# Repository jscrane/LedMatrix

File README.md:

View this project on [CADLAB.io](https://cadlab.io/project/1792). 

# LedMatrix
Simple LED Matrix driver library for LEDs which are driven directly from
GPIOs. Supports square LEDs up to 8x8.

## Requirements
- Arduino 1.8.x
- [SimpleTimer](https://github.com/jfturcot/SimpleTimer) library (for examples)

## Other
See [blog article](https://programmablehardware.blogspot.com/2019/05/soldering-kata.html).

Prototype 7x7 assembled on stripboard:

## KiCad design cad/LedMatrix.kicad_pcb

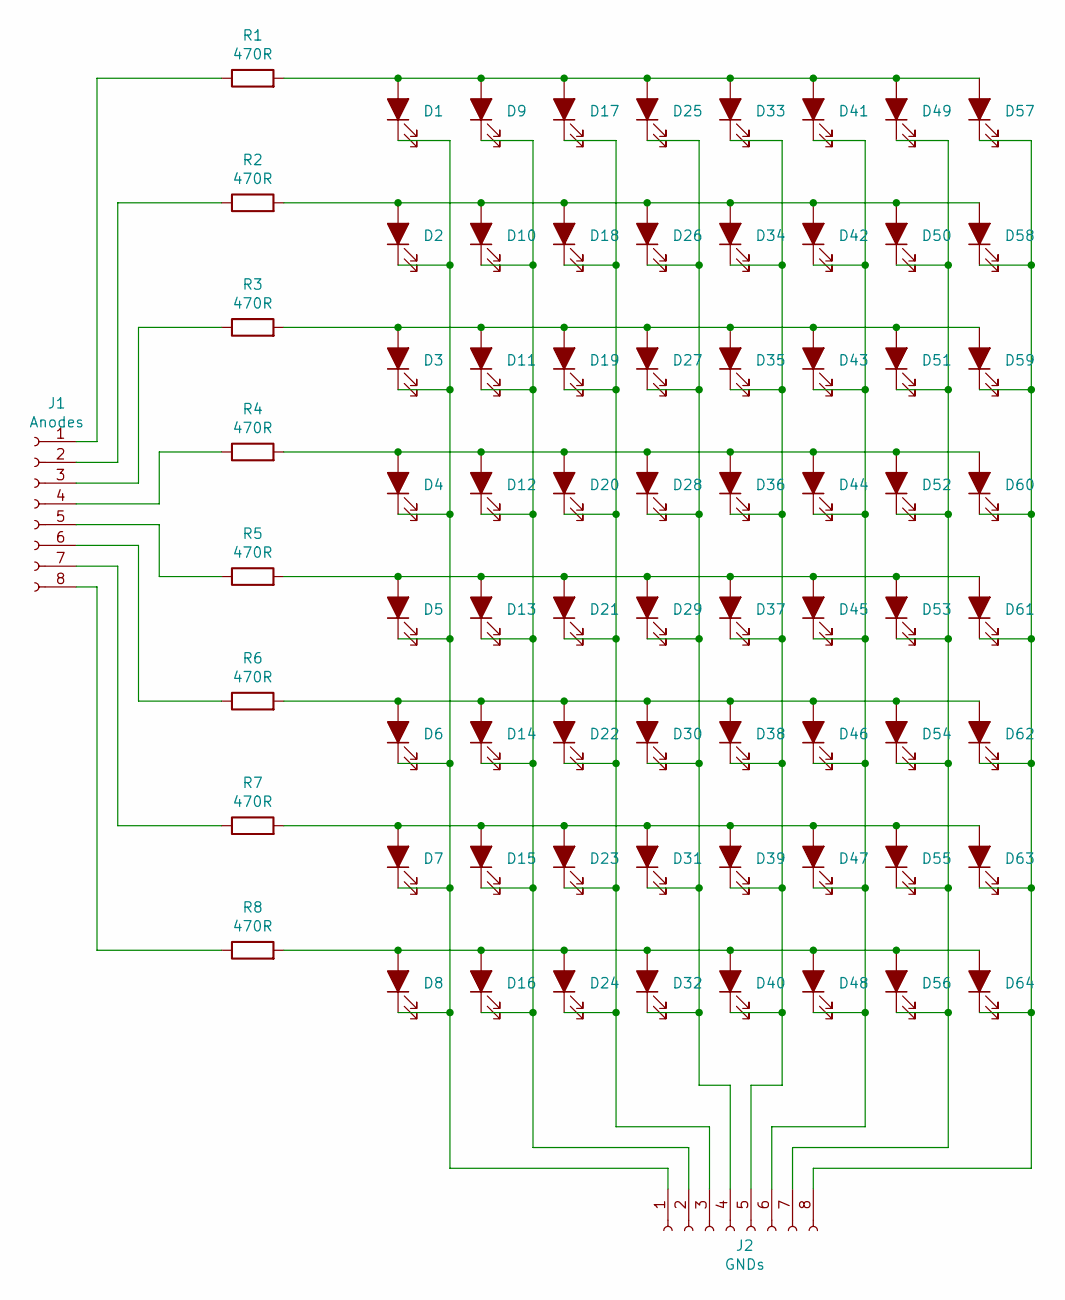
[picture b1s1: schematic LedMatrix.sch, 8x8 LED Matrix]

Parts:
D1, D2, D3, D4, D5, D6, D7, D8, D9, D10, D11, D12, D13, D14, D15, D16, D17, D18, D19, D20, D21, D22, D23, D24, D25, D26, D27, D28, D29, D30, D31, D32, D33, D34, D35, D36, D37, D38, D39, D40, D41, D42, D43, D44, D45, D46, D47, D48, D49, D50, D51, D52, D53, D54, D55, D56, D57, D58, D59, D60, D61, D62, D63, D64: LED_ALT; LED_D3.0mm
J1: Anodes; PinHeader_1x08_P2.54mm_Vertical
J2: GNDs; PinHeader_1x08_P2.54mm_Vertical
R1, R2, R3, R4, R5, R6, R7, R8: 470R; R_Axial_DIN0207_L6.3mm_D2.5mm_P10.16mm_Horizontal

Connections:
unnamed: D1.1 (K), D2.1 (K), D3.1 (K), D4.1 (K), D5.1 (K), D6.1 (K), D7.1 (K), D8.1 (K), J2.1
unnamed: D1.2 (A), D9.2 (A), D17.2 (A), D25.2 (A), D33.2 (A), D41.2 (A), D49.2 (A), D57.2 (A), R1.2
unnamed: D9.1 (K), D10.1 (K), D11.1 (K), D12.1 (K), D13.1 (K), D14.1 (K), D15.1 (K), D16.1 (K), J2.2
unnamed: D2.2 (A), D10.2 (A), D18.2 (A), D26.2 (A), D34.2 (A), D42.2 (A), D50.2 (A), D58.2 (A), R2.2
unnamed: D3.2 (A), D11.2 (A), D19.2 (A), D27.2 (A), D35.2 (A), D43.2 (A), D51.2 (A), D59.2 (A), R3.2
unnamed: D4.2 (A), D12.2 (A), D20.2 (A), D28.2 (A), D36.2 (A), D44.2 (A), D52.2 (A), D60.2 (A), R4.2
unnamed: D5.2 (A), D13.2 (A), D21.2 (A), D29.2 (A), D37.2 (A), D45.2 (A), D53.2 (A), D61.2 (A), R5.2
unnamed: D6.2 (A), D14.2 (A), D22.2 (A), D30.2 (A), D38.2 (A), D46.2 (A), D54.2 (A), D62.2 (A), R6.2
unnamed: D7.2 (A), D15.2 (A), D23.2 (A), D31.2 (A), D39.2 (A), D47.2 (A), D55.2 (A), D63.2 (A), R7.2
unnamed: D8.2 (A), D16.2 (A), D24.2 (A), D32.2 (A), D40.2 (A), D48.2 (A), D56.2 (A), D64.2 (A), R8.2
unnamed: D17.1 (K), D18.1 (K), D19.1 (K), D20.1 (K), D21.1 (K), D22.1 (K), D23.1 (K), D24.1 (K), J2.3
unnamed: D25.1 (K), D26.1 (K), D27.1 (K), D28.1 (K), D29.1 (K), D30.1 (K), D31.1 (K), D32.1 (K), J2.4
unnamed: D33.1 (K), D34.1 (K), D35.1 (K), D36.1 (K), D37.1 (K), D38.1 (K), D39.1 (K), D40.1 (K), J2.5
unnamed: D41.1 (K), D42.1 (K), D43.1 (K), D44.1 (K), D45.1 (K), D46.1 (K), D47.1 (K), D48.1 (K), J2.6
unnamed: D49.1 (K), D50.1 (K), D51.1 (K), D52.1 (K), D53.1 (K), D54.1 (K), D55.1 (K), D56.1 (K), J2.7
unnamed: D57.1 (K), D58.1 (K), D59.1 (K), D60.1 (K), D61.1 (K), D62.1 (K), D63.1 (K), D64.1 (K), J2.8
unnamed: J1.1, R1.1
unnamed: J1.2, R2.1
unnamed: J1.3, R3.1
unnamed: J1.4, R4.1
unnamed: J1.5, R5.1
unnamed: J1.6, R6.1
unnamed: J1.7, R7.1
unnamed: J1.8, R8.1

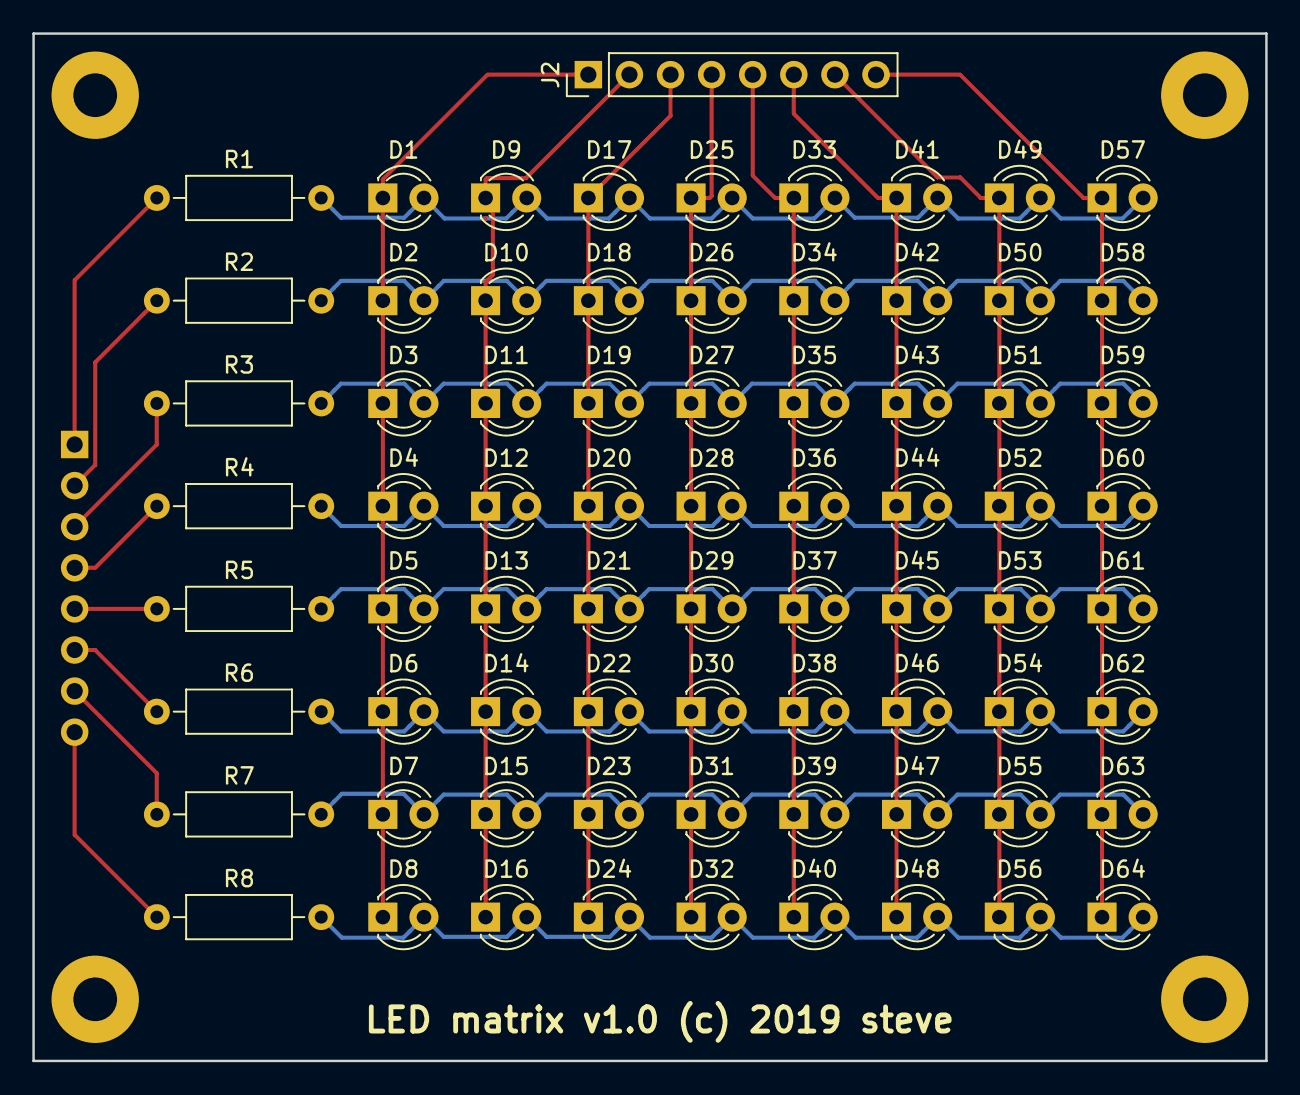
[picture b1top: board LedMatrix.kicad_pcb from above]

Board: 2 copper layers, 76.2 x 63.5 mm, 74 parts (1 on the bottom side), 24 nets.

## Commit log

2019-05-21 add .cpp
2019-05-21 add example
2019-05-21 scale image
2019-05-21 initial kicad schematic
2019-05-21 Backlink to CADLAB.io has been added.
2019-05-22 add netlist
2019-05-22 initial layout
2019-05-22 compact layout
2019-05-22 tracks
2019-05-22 better pictures
2019-05-22 blog
2019-05-25 board outline
2019-05-26 gerbers
2019-05-26 gerbers for seeed
2019-05-27 renaming privates
2019-05-27 Scroller example
2019-05-27 cleanup
2019-06-12 add drill holes
2019-06-18 v1.0 gerbers
2019-07-18 update for 8x8 matrix

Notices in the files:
cad/LedMatrix.kicad_pcb:
LED matrix v1.0 (c) 2019 steve
